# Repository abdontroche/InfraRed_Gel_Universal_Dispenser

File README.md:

=================================
This project pretends to be a open source device that could help people fighting against the COVID-19.
# Who are we?
*Estimados Miembros: Este grupo está conformado por alumnos, profesores y egresados de la FP-UNA y tiene por objetivo pensar, formular y realizar acciones concretas ante esta situación adversa que vivimos en el país con respecto al coronavirus COVID-19. Iniciamos con gente del área de electrónica e informática pero no estamos cerrados de ninguna manera. El trabajo es voluntario y sin fines de lucro. A hombros de gigantes enfrentaremos mejor las adversidades.*

Dear Members: This group is made up of students, professors and graduates of the FP-UNA and its objective is to think, formulate and carry out concrete actions in the face of this adverse situation that we are experiencing in the country with respect to the COVID-19 coronavirus. We started with people from the electronics and computing area but we are not closed in any way. The work is voluntary and non-profit. On the shoulders of giants we will better face adversities.

Team FP-UNA/COVID

# What we want to achieve?
The board is based on the website called [www.electroschematics.com](www.electroschematics.com) and the project is called [Automatic soap dispenser IR proximity sensor](https://www.electroschematics.com/automatic-soap-dispenser-ir-proximity-sensor/).

We want to use this board and use to dispense gel alcohol adapting it on differents bottles. 

# What we will find inside this repository?

Fist to all we will find the board.

The Board was designed using the software [KiCad 5.1.2](https://www.kicad.org)

The components are chosen by the existence on the Paraguay electronics componentes market.

## The schmematic

## The board

## Bill Of Materials
This is the file of the [BOM](InfraRedGelUniversalDispenser/bom/ibom.html)

## The 3D models

You will find the board 3D model in the STP format in order you can choose the software you want to develope the mechanism with.

### Desing the mechanism using [Fusion 360](https://www.autodesk.com/products/fusion-360/students-teachers-educators)

#### Electronic board

#### [Dispenser mecanism](InfraRedGelUniversalDispenser/CustomizedSolenoid v5.step)

#### [Gel alcohol bottle or soap bottle dispenser](https://grabcad.com/library/soap-dispenser-5)

#### Fisrt assembly

#### Second assembly

File of the prototipe "InfraRedGelUniversalDispenserDevice v17.step"

# This is another version of the board
## The schmematic

## The board

## Bill Of Materials

## The 3D models

You will find the board 3D model in the STP format in order you can choose the software you want to develope the mechanism with.

### Desing the mechanism using [Fusion 360](https://www.autodesk.com/products/fusion-360/students-teachers-educators)

#### Electronic board

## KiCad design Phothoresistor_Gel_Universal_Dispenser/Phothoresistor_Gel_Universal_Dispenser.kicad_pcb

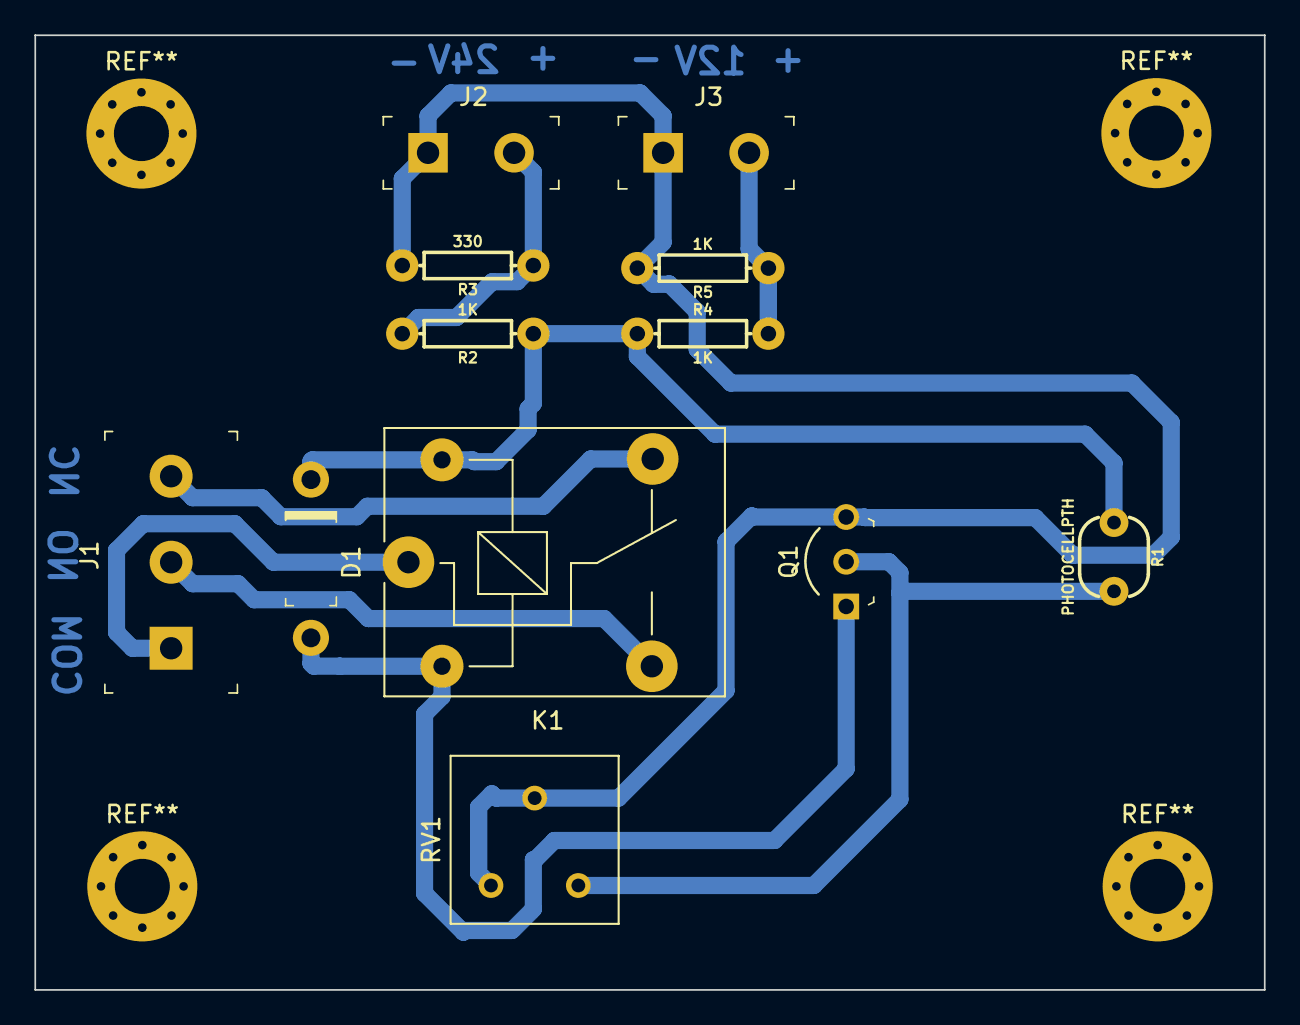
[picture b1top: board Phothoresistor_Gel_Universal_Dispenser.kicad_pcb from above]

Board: 2 copper layers, 71.5 x 55.5 mm, 12 parts (0 on the bottom side), 9 nets.

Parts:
D1: 1N4007-T_NRND; DO-41
J1: OSTTC030162; Term_Block_1x3_P5mm
J2: 24V; Terminal_Block_D1.3mm_P5mm
J3: 12V; Terminal_Block_D1.3mm_P5mm
K1: SANYOU_SRD_Form_C; Relay_SPDT_SANYOU_SRD_Series_Form_C
Q1: BC548CTA; TO-92-3_Formed_Leads
R1: PHOTOCELLPTH; PHOTOCELL
R2, R4, R5: 1K; AXIAL-0.3
R3: 330; AXIAL-0.3
RV1: 10K; Potentiometer_Bourns_3386F_Vertical

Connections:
GND: J2.1, J3.1, Q1.3, R3.P$2, R5.P$2, RV1.2, RV1.3
unnamed: D1.A, K1.2, Q1.1
unnamed: J1.1, K1.1
unnamed: J1.2, K1.3
unnamed: J1.3, K1.4
unnamed: J2.2, R2.P$2, R3.P$1
unnamed: J3.2, R4.P$2, R5.P$1
unnamed: Q1.2, R1.2, RV1.1
VCC: D1.K, K1.5, R1.1, R2.P$1, R4.P$1

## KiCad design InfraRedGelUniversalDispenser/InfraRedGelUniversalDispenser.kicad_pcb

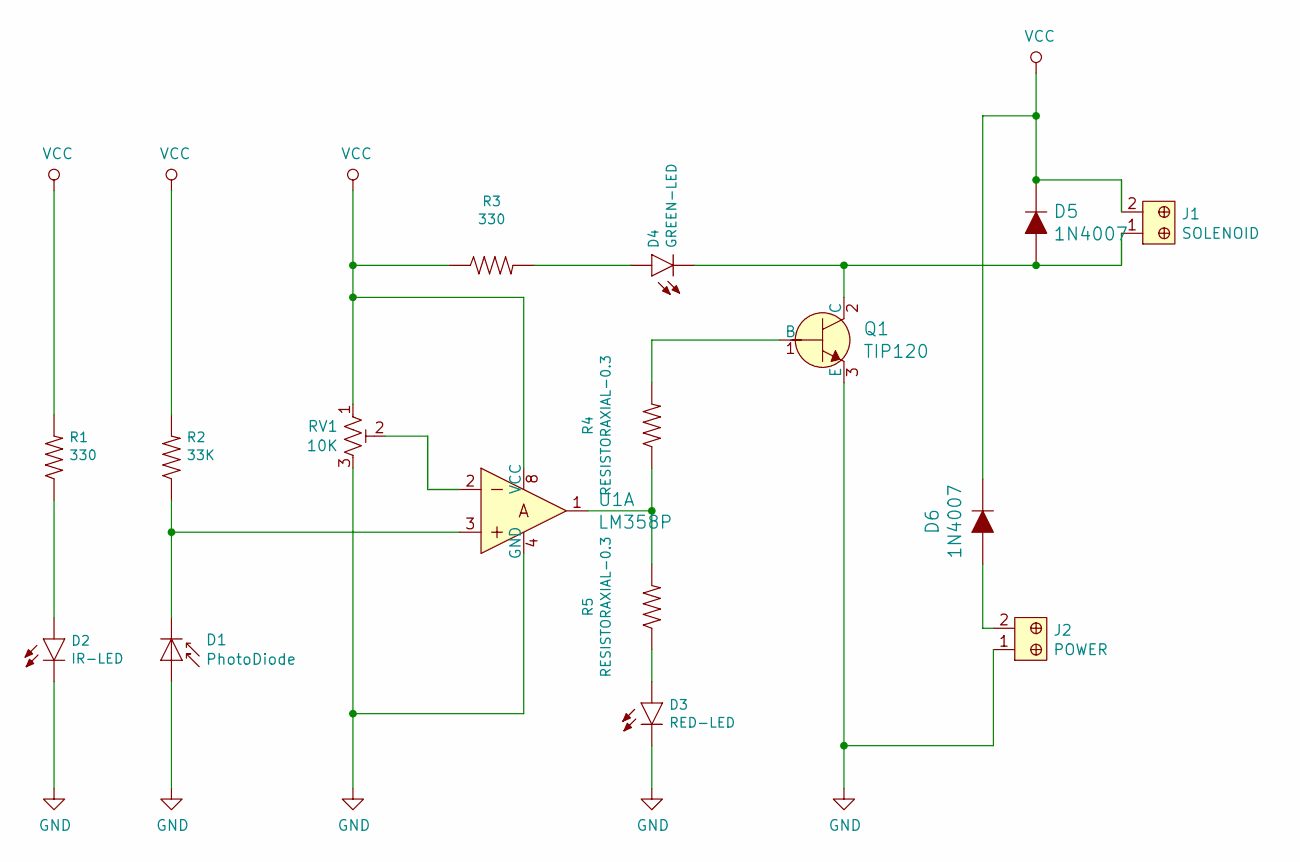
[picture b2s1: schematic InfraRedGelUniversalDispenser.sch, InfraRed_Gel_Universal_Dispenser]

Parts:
D1: PhotoDiode; LED_D5.0mm_IRGrey
D2: IR-LED; LED_5MM-KIT
D3: RED-LED; LED_5MM-KIT
D4: GREEN-LED; LED_5MM-KIT
D5, D6: 1N4007; DO-41; MPN 1N4007-T; Digi-Key_PN 1N4007DICT-ND
J1: SOLENOID; Term_Block_1x2_P5mm; MPN OSTTC020162; Digi-Key_PN ED2600-ND
J2: POWER; Term_Block_1x2_P5mm; MPN OSTTC020162; Digi-Key_PN ED2600-ND
Q1: TIP120; TO-220-3; MPN TIP120; Digi-Key_PN 497-2539-5-ND
R1, R3: 330; AXIAL-0.3
R2: 33K; AXIAL-0.3
R4, R5: RESISTORAXIAL-0.3; AXIAL-0.3
RV1: 10K; Potentiometer_Bourns_3386F_Vertical
U1: LM358P; DIP-8_W7.62mm; MPN LM358P; Digi-Key_PN 296-1395-5-ND

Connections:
GND: D1.2 (A), D2.K (C), D3.K (C), J2.1, Q1.3 (E), RV1.3, U1.4 (GND)
unnamed: D1.1 (K), R2.P$1 (1), U1.3
unnamed: D2.A, R1.P$1 (1)
unnamed: D3.A, R5.P$1 (1)
unnamed: D4.A, R3.P$2 (2)
unnamed: D4.K (C), D5.A, J1.1, Q1.2 (C)
unnamed: D6.A, J2.2
unnamed: Q1.1 (B), R4.P$2 (2)
unnamed: R4.P$1 (1), R5.P$2 (2), U1.1
unnamed: RV1.2, U1.2
VCC: D5.K, D6.K, J1.2, R1.P$2 (2), R2.P$2 (2), R3.P$1 (1), RV1.1, U1.8 (VCC)

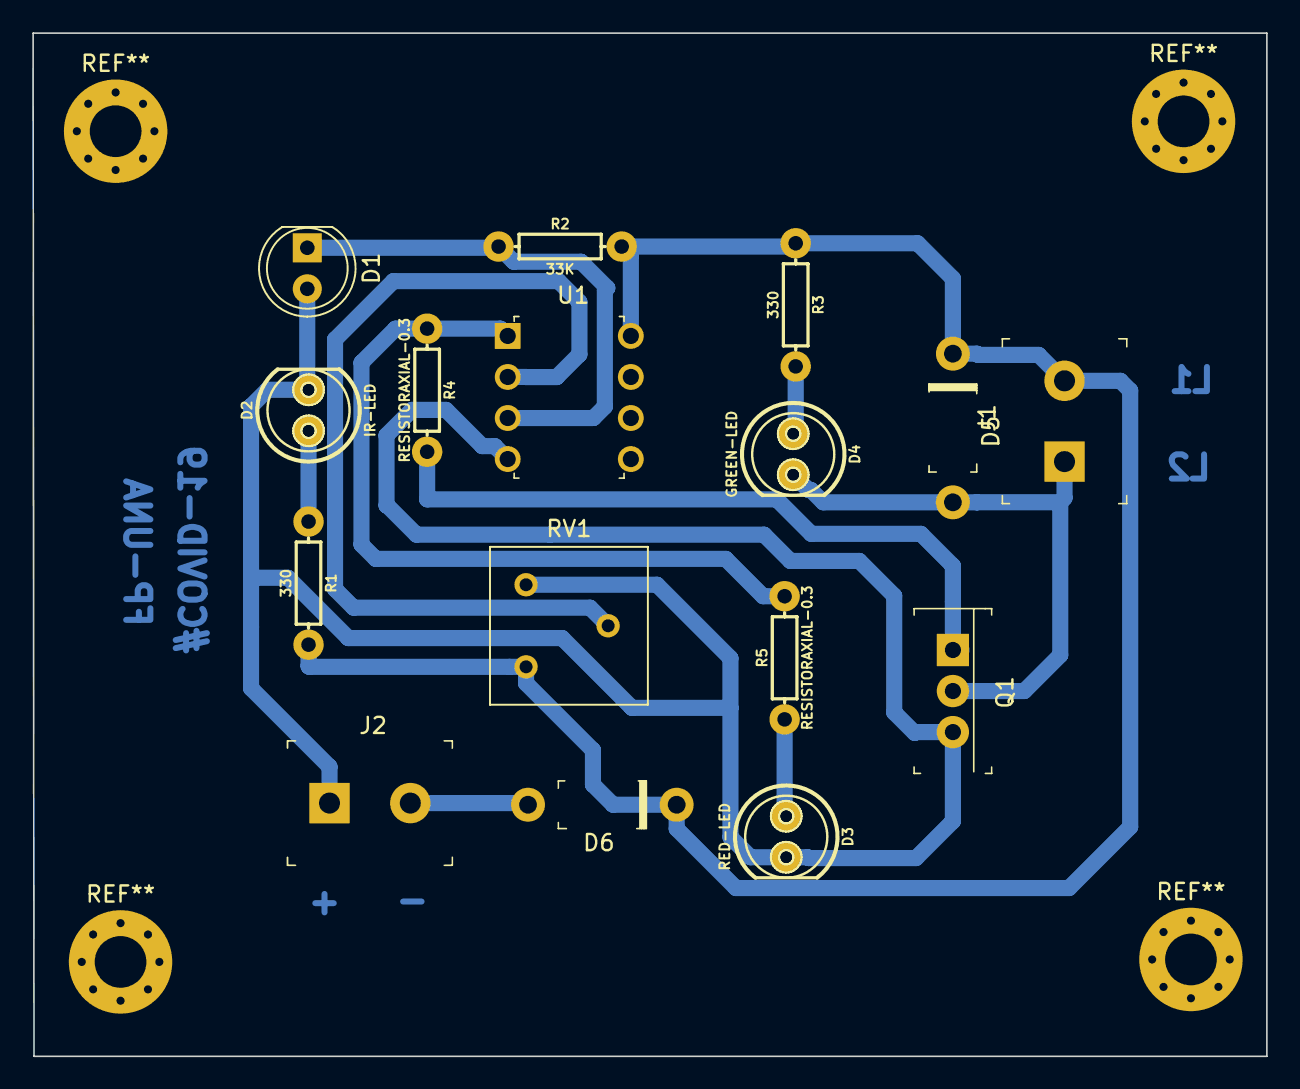
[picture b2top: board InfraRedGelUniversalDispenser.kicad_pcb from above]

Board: 2 copper layers, 76.4 x 63.3 mm, 16 parts (0 on the bottom side), 11 nets.

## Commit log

2020-03-15 I added all the files related to the opensource project called InfraredUniversalGelDispenserDevice
2020-03-15 I added description to the readme in orther to make easy the reading to any who wants to work in the project
2020-03-15 I created the mechanism for the dispenser and also generated the bill of materials for make the budget
2020-03-16 I finished the prototipe of the device and it is ready for fabrication
2020-03-22 I designed a new version of the sensor with LDR simpler than the last one
2020-03-22 I added readme information about the new version of the board
2021-11-09 Update README.md
    https://forum.kicad.info/t/warning-avoid-all-links-to-kicad-pcb-org-use-kicad-org/31521

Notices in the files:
InfraRedGelUniversalDispenser/InfraRedGelUniversalDispenser.kicad_pcb:
License: CC BY 4.0
